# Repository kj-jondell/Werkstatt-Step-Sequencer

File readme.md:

# What is this?
A CV/Osc eight-step sequencer based on STM32 'Black Pill'. Designed for the Moog Werkstatt-01.

Gerber-files and Arduino code will be available.

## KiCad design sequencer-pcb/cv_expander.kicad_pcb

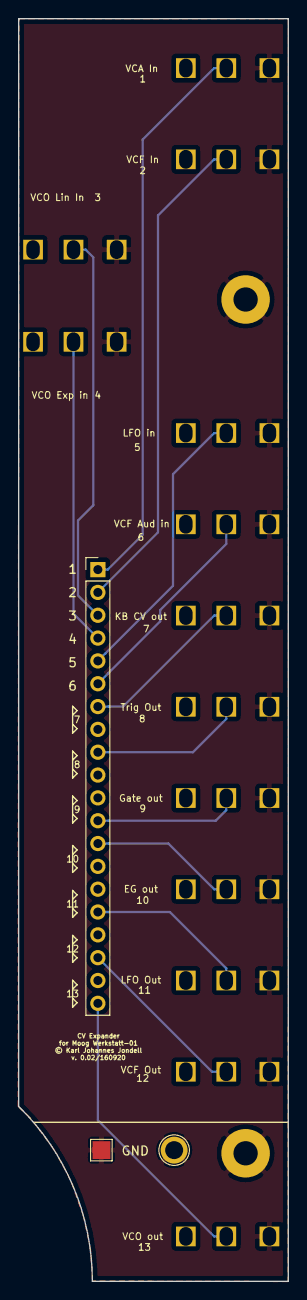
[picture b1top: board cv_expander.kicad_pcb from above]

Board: 2 copper layers, 30.0 x 140.5 mm, 18 parts (0 on the bottom side), 14 nets.

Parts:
GND: MountingHole_GND; MountingHole_2.7mm_M2.5_Pad
GND#2: TestPoint; TestPoint_Plated_Hole_D2.0mm
H1: MountingHole_GND; MountingHole_2.7mm_M2.5_Pad
J1: Conn_01x20_Male; PinHeader_1x20_P2.54mm_Vertical
J2: VCA In; 3.5mm_Electrokit
J3: VCF In; 3.5mm_Electrokit
J4: VCO Lin In; 3.5mm_Electrokit
J5: VCO Exp in; 3.5mm_Electrokit
J6: LFO in; 3.5mm_Electrokit
J7: VCF Aud in; 3.5mm_Electrokit
J8: KB CV out; 3.5mm_Electrokit
J9: Trig Out; 3.5mm_Electrokit
J10: Gate out; 3.5mm_Electrokit
J11: EG out; 3.5mm_Electrokit
J12: LFO Out; 3.5mm_Electrokit
J13: VCF Out; 3.5mm_Electrokit
J14: VCO out; 3.5mm_Electrokit
TP2: TestPoint; TestPoint_Pad_2.0x2.0mm

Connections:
GND_D: GND.1, GND#2.1, H1.1, J2.S, J3.S, J4.S, J5.S, J6.S, J7.S, J8.S, J9.S, J10.S, J11.S, J12.S, J13.S, J14.S, TP2.1
unnamed: J1.1, J2.T
unnamed: J1.2, J3.T
unnamed: J1.3, J4.T
unnamed: J1.4, J5.T
unnamed: J1.5, J6.T
unnamed: J1.6, J7.T
unnamed: J1.7, J1.8, J8.T
unnamed: J1.9, J1.10, J9.T
unnamed: J1.11, J1.12, J10.T
unnamed: J1.13, J1.14, J11.T
unnamed: J1.15, J1.16, J12.T
unnamed: J1.17, J1.18, J13.T
unnamed: J1.19, J1.20, J14.T

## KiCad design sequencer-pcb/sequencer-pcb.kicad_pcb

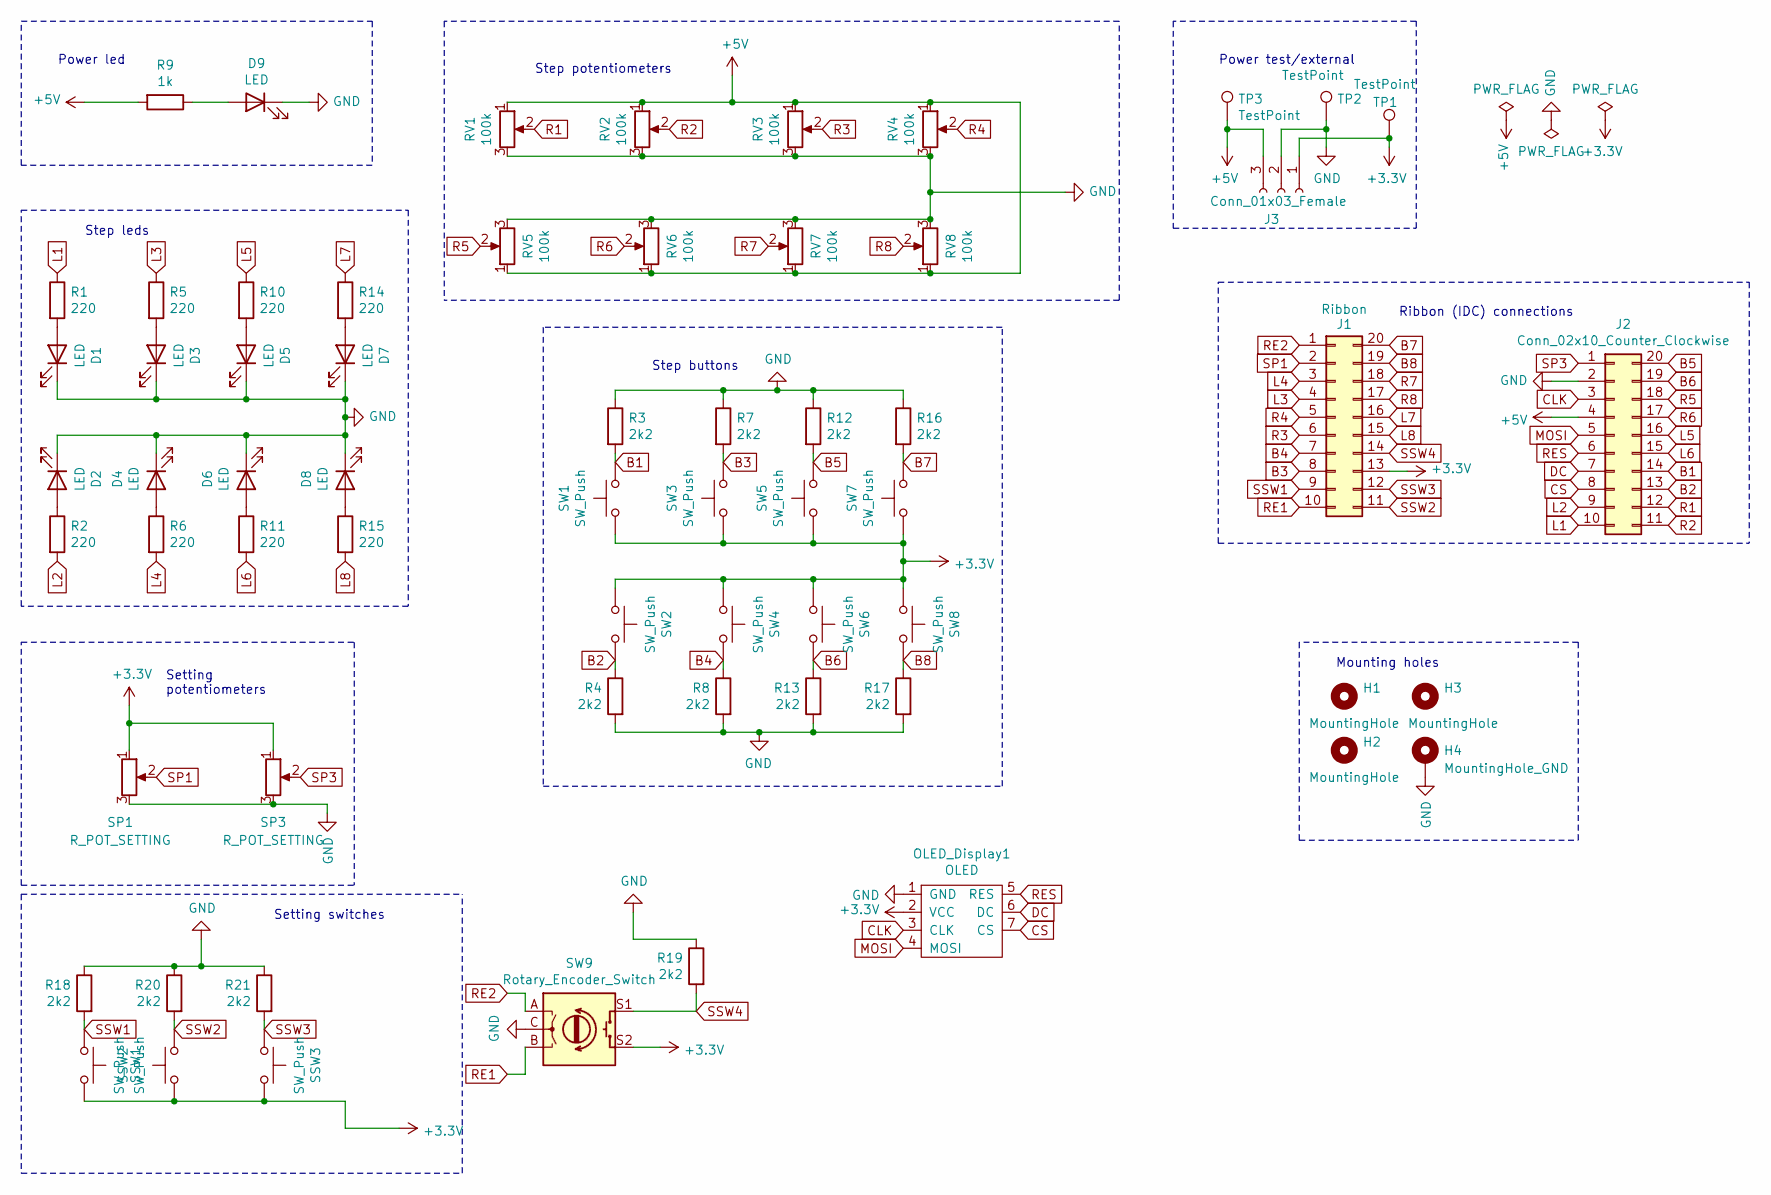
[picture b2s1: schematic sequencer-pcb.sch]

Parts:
D1, D2, D3, D4, D5, D6, D7, D8: LED; LED_D5.0mm
D9: LED; LED_1206_3216Metric_Pad1.42x1.75mm_HandSolder
H1, H2, H3: MountingHole; MountingHole_2.7mm_M2.5
H4: MountingHole_GND; MountingHole_2.7mm_M2.5_Pad
J1: Ribbon; IDC-Header_2x10_P2.54mm_Vertical
J2: Conn_02x10_Counter_Clockwise; IDC-Header_2x10_P2.54mm_Vertical
J3: Conn_01x03_Female; PinHeader_1x03_P2.54mm_Vertical
OLED_Display1: OLED; OLED_SPI_128x32
R1, R2, R5, R6, R10, R11, R14, R15: 220; R_1206_3216Metric_Pad1.42x1.75mm_HandSolder
R3, R4, R7, R8, R12, R13, R16, R17, R18, R19, R20, R21: 2k2; R_1206_3216Metric_Pad1.42x1.75mm_HandSolder
R9: 1k; R_1206_3216Metric_Pad1.42x1.75mm_HandSolder
RV1, RV2, RV3, RV4, RV5, RV6, RV7, RV8: 100k; Potentiometer_Alps_RK09K_Single_Vertical
SP1, SP3: R_POT_SETTING; Potentiometer_Alps_RK09K_Single_Vertical
SSW1, SSW2, SSW3: SW_Push; SW_PUSH_6mm_H5mm
SW1, SW2, SW3, SW4, SW5, SW6, SW7, SW8: SW_Push; SW_PUSH_6mm_H5mm
SW9: Rotary_Encoder_Switch; RotaryEncoder_Alps_EC12E-Switch_Vertical_H20mm
TP1, TP2, TP3: TestPoint; TestPoint_THTPad_2.5x2.5mm_Drill1.2mm

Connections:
+3V3: J1.13, J3.1, OLED_Display1.2 (VCC), SP1.1, SP3.1, SSW1.1, SSW2.2, SSW3.1, SW1.1, SW2.1, SW3.1, SW4.1, SW5.1, SW6.1, SW7.1, SW8.1, SW9.S2, TP1.1
+5V: J2.4, J3.3, R9.2, RV1.1, RV2.1, RV3.1, RV4.1, RV5.1, RV6.1, RV7.1, RV8.1, TP3.1
B1: J2.14, R3.2, SW1.2
B2: J2.13, R4.1, SW2.2
B3: J1.8, R7.2, SW3.2
B4: J1.7, R8.1, SW4.2
B5: J2.20, R12.2, SW5.2
B6: J2.19, R13.1, SW6.2
B7: J1.20, R16.2, SW7.2
B8: J1.19, R17.1, SW8.2
CLK: J2.3, OLED_Display1.3 (CLK)
CS: J2.8, OLED_Display1.7 (CS)
DC: J2.7, OLED_Display1.6 (DC)
GND: D1.1 (K), D2.1 (K), D3.1 (K), D4.1 (K), D5.1 (K), D6.1 (K), D7.1 (K), D8.1 (K), D9.1 (K), H4.1, J2.2, J3.2, OLED_Display1.1 (GND), R3.1, R4.2, R7.1, R8.2, R12.1, R13.2, R16.1, R17.2, R18.1, R19.1, R20.1, R21.1, RV1.3, RV2.3, RV3.3, RV4.3, RV5.3, RV6.3, RV7.3, RV8.3, SP1.3, SP3.3, SW9.C, TP2.1
L1: J2.10, R1.1
L2: J2.9, R2.2
L3: J1.4, R5.1
L4: J1.3, R6.2
L5: J2.16, R10.1
L6: J2.15, R11.2
L7: J1.16, R14.1
L8: J1.15, R15.2
MOSI: J2.5, OLED_Display1.4 (MOSI)
unnamed: D1.2 (A), R1.2
unnamed: D2.2 (A), R2.1
unnamed: D3.2 (A), R5.2
unnamed: D4.2 (A), R6.1
unnamed: D5.2 (A), R10.2
unnamed: D6.2 (A), R11.1
unnamed: D7.2 (A), R14.2
unnamed: D8.2 (A), R15.1
unnamed: D9.2 (A), R9.1
R1: J2.12, RV1.2
R2: J2.11, RV2.2
R3: J1.6, RV3.2
R4: J1.5, RV4.2
R5: J2.18, RV5.2
R6: J2.17, RV6.2
R7: J1.18, RV7.2
R8: J1.17, RV8.2
RE1: J1.10, SW9.B
RE2: J1.1, SW9.A
RES: J2.6, OLED_Display1.5 (RES)
SP1: J1.2, SP1.2
SP3: J2.1, SP3.2
SSW1: J1.9, R18.2, SSW1.2
SSW2: J1.11, R20.2, SSW2.1
SSW3: J1.12, R21.2, SSW3.2
SSW4: J1.14, R19.2, SW9.S1

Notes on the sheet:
Power led
Step potentiometers
Ribbon (IDC) connections
Power test/external
Step leds
Step buttons
Mounting holes
Setting potentiometers
Setting switches

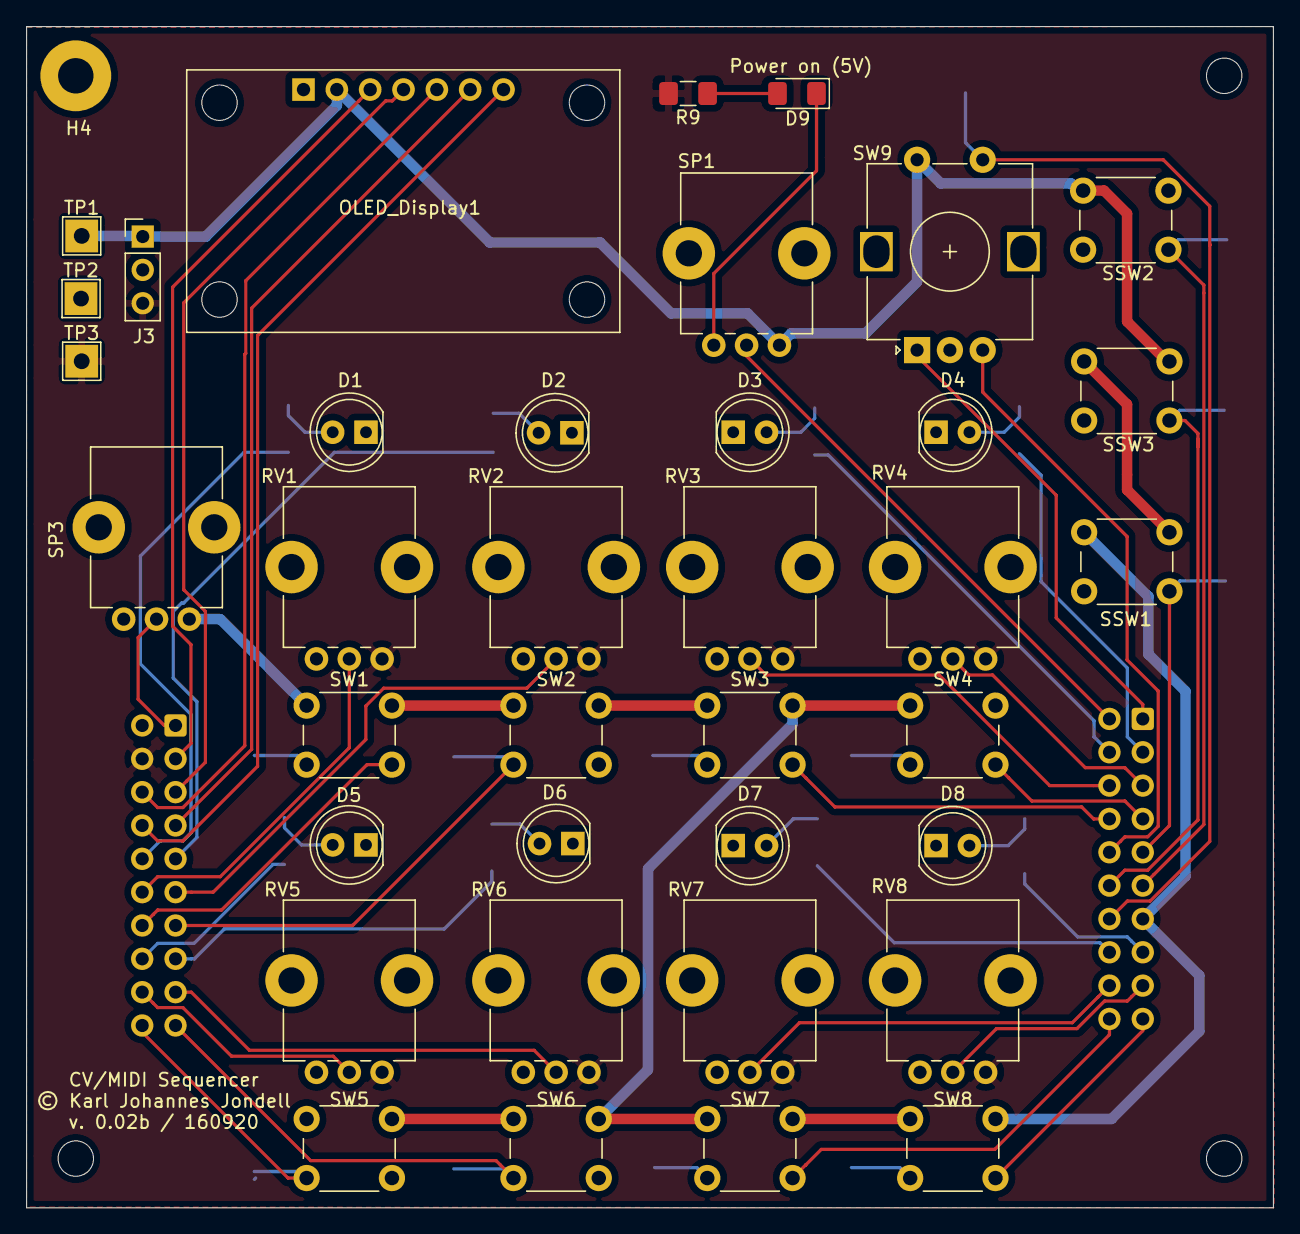
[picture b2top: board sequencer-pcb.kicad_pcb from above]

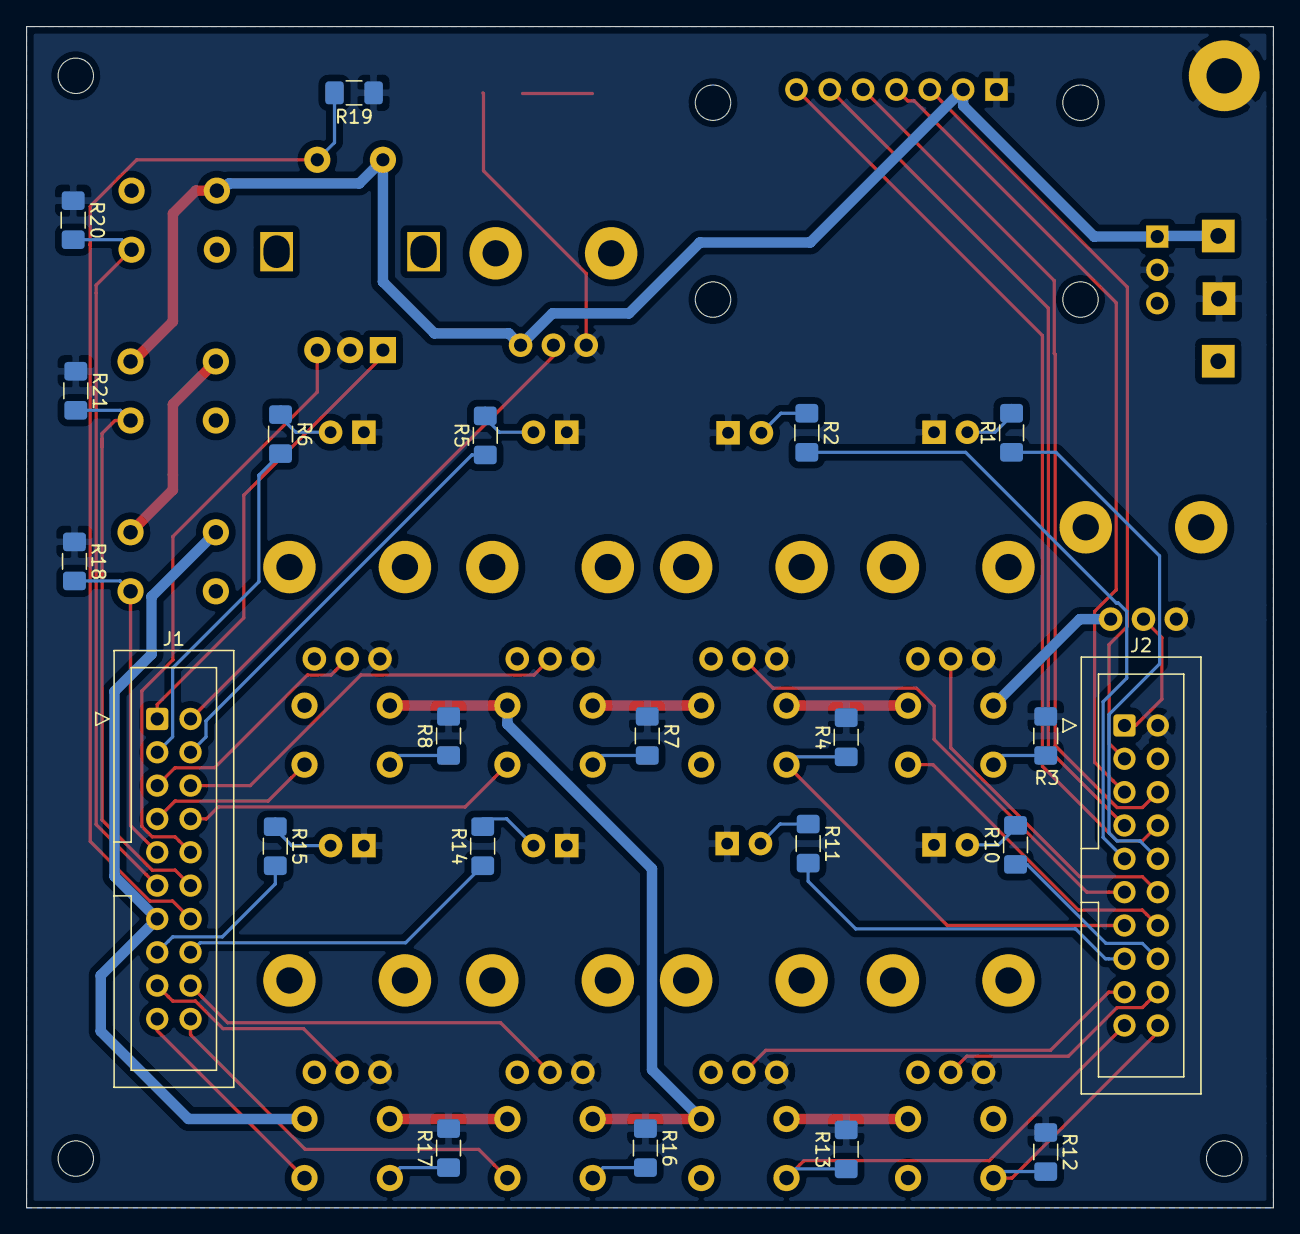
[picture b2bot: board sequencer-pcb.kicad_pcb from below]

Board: 2 copper layers, 95.0 x 90.0 mm, 63 parts (22 on the bottom side), 49 nets.

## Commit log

2017-08-03 first commit!
    arduino code to step sequencer.
2017-08-03 new structure
    new file structure
2017-08-05 updated support for different note values
2017-08-05 EDIT MODE fixed
2017-08-14 new updated firmware!
2017-08-17 rock n roll!!!
2020-08-05 preparation for new version
2020-08-05 readme
2020-08-05 arduino code
2020-08-07 pcb changes
2020-08-07 updates pcb and schematic
2020-08-07 sync recorded
2020-08-16 kicad updates
2020-08-19 sync
2020-08-21 code for reading pot input
2020-08-21 pot inputs
2020-08-29 sequencer
2020-08-29 new pcb
2020-08-30 new led
2020-08-31 gerbers
2020-09-15 boms
2020-09-17 cv expander
2020-09-17 expander
2020-09-17 gitignore

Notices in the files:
sequencer-pcb/cv_expander.kicad_pcb:
© Karl Johannes Jondell
